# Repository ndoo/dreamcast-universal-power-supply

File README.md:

# Dreamcast Universal Power Supply

Universal AC to DC power supply for the Dreamcast (no 12V)

## Bill of Materials

| Component | Manufacturer | Part Number                                       | Value |
|-----------|--------------|---------------------------------------------------|-------|
| J1        | EDK          | AC-M15PB79 (desolder from existing PSU)           |       |
| J2        | TE           | 1-1123724-2                                       |       |
| J3        | Molex        | 09-52-3062                                        |       |
| U1        | Diodes Inc   | AP1501A-33K5G-13                                  |       |
| U2        | Mean Well    | IRM-20-5                                          |       |
| CT1,CT2   | Panasonic    | EEE-FK0J471P                                      | 470uF |
| L1        | Bourns       | SRR1208-180ML                                     | 18uH  |
| D1        |              | DO-214AA SMT Schottky diode rated at least 5A/20V |       |

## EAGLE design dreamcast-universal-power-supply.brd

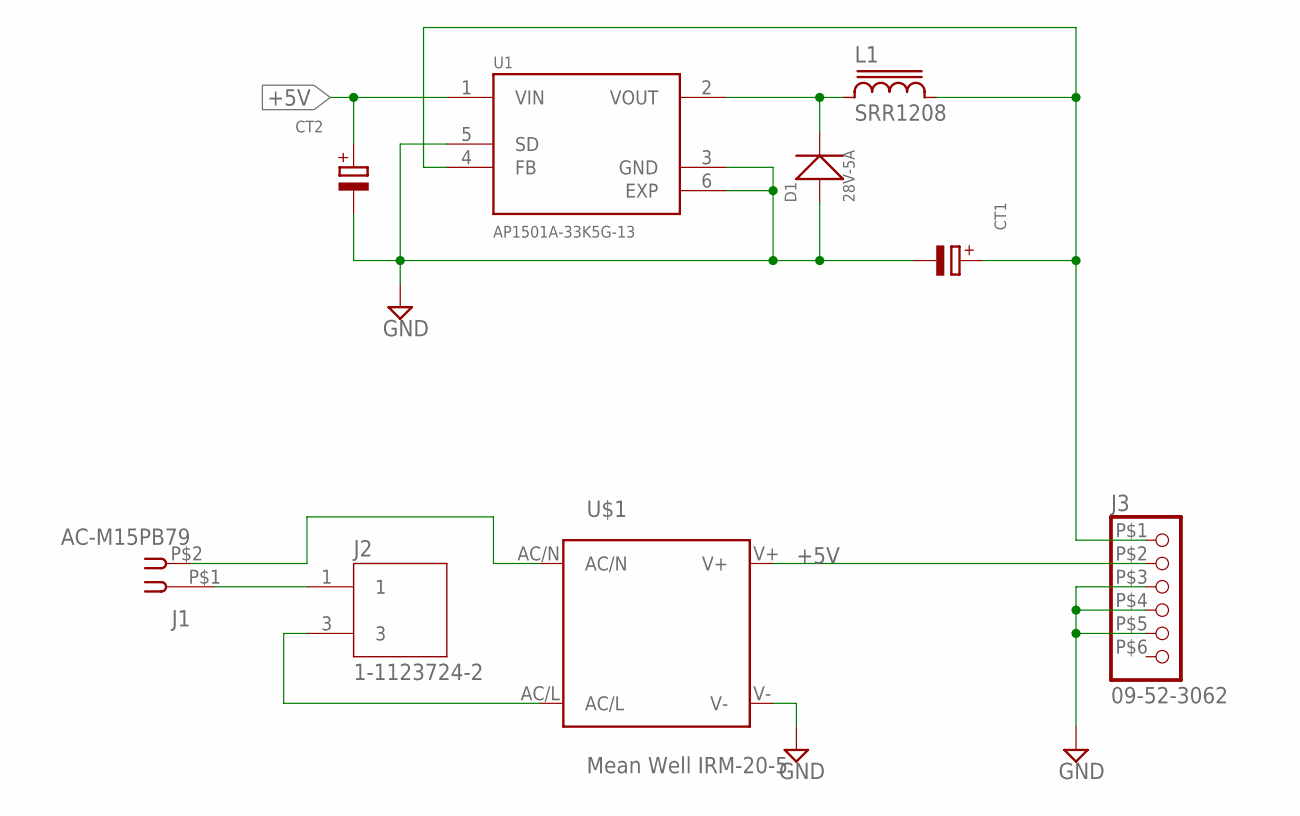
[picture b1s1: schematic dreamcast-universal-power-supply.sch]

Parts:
CT1, CT2: C-POL_ECAP-8.5MM; CAPAE830X1050N
D1: 28V-5A; DO-214AA
J1: AC-M15PB79
J2: 1-1123724-2; TE_1-1123724-2
J3: 09-52-3062
L1: SRR1208; SSR1208
U1: AP1501A-33K5G-13; DPAK171P1524X485-6N
U$1: Mean Well IRM-20-5; IRM_15/20

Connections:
1: J1.P$1 (1), J2.1
2: J1.P$2 (2), U$1.AC/N
+5V: CT2.1 (+), J3.P$2 (2), U1.1 (VIN), U$1.V+
GND: CT1.2 (-), CT2.2 (-), D1.+, J3.P$3 (3), J3.P$4 (4), J3.P$5 (5), U1.3 (GND), U1.5 (SD), U1.6 (EXP), U$1.V-
unnamed: J2.3, U$1.AC/L
unnamed: D1.-, L1.1, U1.2 (VOUT)
unnamed: CT1.1 (+), J3.P$1 (1), L1.2, U1.4 (FB)

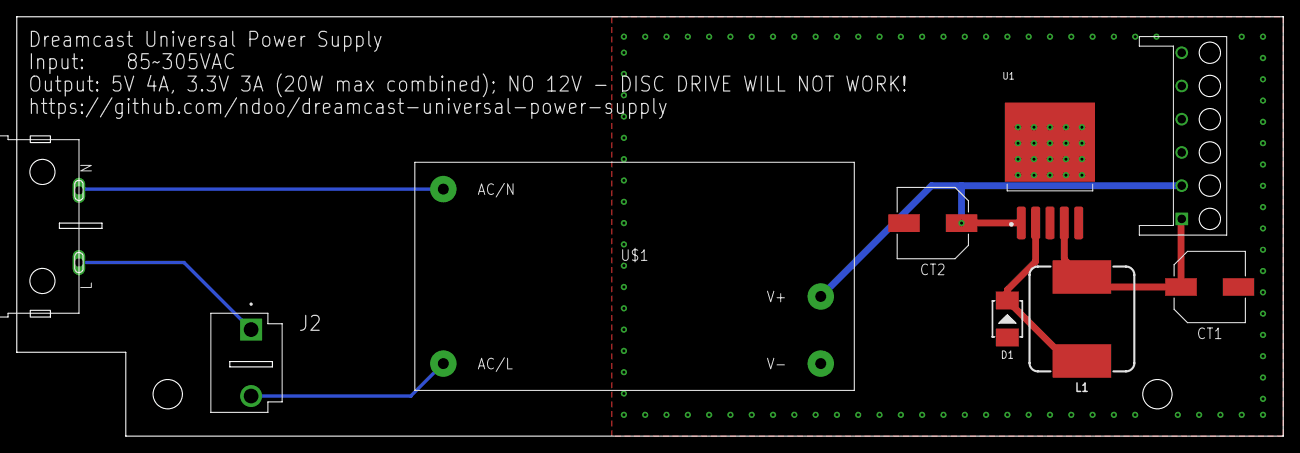
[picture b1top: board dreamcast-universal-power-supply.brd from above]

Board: 2 copper layers, 151.0 x 50.0 mm, 9 parts (0 on the bottom side), 7 nets.

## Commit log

2020-07-08 Add warning about no 12V supply and that disc drive will not work with this power supply
2020-07-08 Remove Eagle backups from repo
2020-07-08 Add board image
2020-07-08 README: Add bill of materials

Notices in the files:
parts and their libraries:
inductor-bourns: Copyright (C) 2008, Bob Starr
